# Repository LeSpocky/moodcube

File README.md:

MoodCube
========

What's This?
------------

With mood39 aka Starterkit from [Netz39](http://www.netz39.de/) and the
[infinity mirror cube](http://www.netz39.de/projekte/infinitiy-mirror-cube/) 
from Frank in mind I designed a mood lamp with five RGB LEDs, three
potentiometers and an ATtiny 24/44 controller.

Circuits
--------

Eagle files for both types of PCB are included. One is the base with the
microcontroller and the potentiometers. VCC is intended to be 5V,
however in the first prototype there's no voltage control circuit on
this pcb, so you have to connect a stabilized power supply.

The other one is a PCB for the LED. Current is hold constant by a simple
constant current circuit per color channel. The connection is simply one
cable per channel plus VCC and GND. uC I/O ports are directly connected
to the color lines.

Housing
-------

The housing in the prototype was 6mm plexiglass milled on a CNC machine.
Holding it together was forgotten in design, but the OpenSCAD files are
added here anyway. Simply glueing them is one solution. You could also
make a base plate or anything else.

LED-PCB Mount
-------------

For the prototype I used a frame construction printed with a 3D printer
and lots of hot melt glue. However this was far from optimal and should
not repeated! Please think up a better solution and let me know!

Part List
---------
/tbd/

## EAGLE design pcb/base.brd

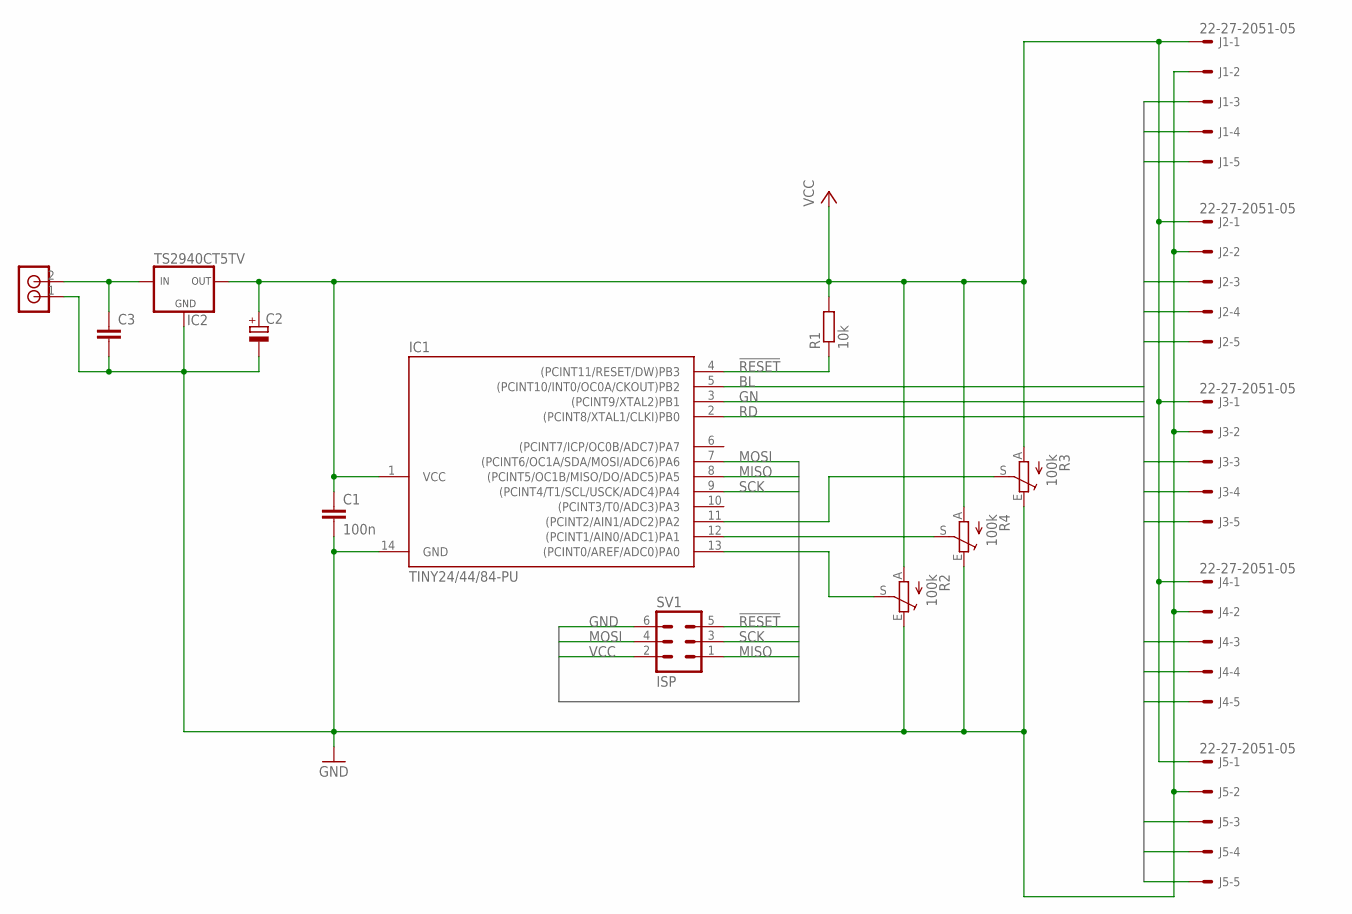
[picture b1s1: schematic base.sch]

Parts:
C1: 100n; C0805
C2: CPOL-EUE2.5-7; E2,5-7
C3: C-EU025-025X050; C025-025X050
IC1: TINY24/44/84-PU; DIL14
IC2: TS2940CT5TV; TO220V
J1, J2, J3, J4, J5: 22-27-2051-05; 6410-05
R1: 10k; R0805
R2, R3, R4: 100k; CIP20C-6MM
SV1: ISP; ML6
U$9: RIACON_101_2

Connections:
!RESET: IC1.4 ((PCINT11/RESET/DW)PB3), R1.1, SV1.5
BL: IC1.5 ((PCINT10/INT0/OC0A/CKOUT)PB2), J1.5, J2.5, J3.5, J4.5, J5.5
GN: IC1.3 ((PCINT9/XTAL2)PB1), J1.4, J2.4, J3.4, J4.4, J5.4
GND: C1.2, C2.-, C3.2, IC1.14 (GND), IC2.2 (GND), J1.2, J2.2, J3.2, J4.2, J5.2, R2.E, R3.E, R4.E, SV1.6, U$9.1
MISO: IC1.8 ((PCINT5/OC1B/MISO/DO/ADC5)PA5), SV1.1
MOSI: IC1.7 ((PCINT6/OC1A/SDA/MOSI/ADC6)PA6), SV1.4
unnamed: IC1.13 ((PCINT0/AREF/ADC0)PA0), R2.S
unnamed: IC1.12 ((PCINT1/AIN0/ADC1)PA1), R4.S
unnamed: IC1.11 ((PCINT2/AIN1/ADC2)PA2), R3.S
unnamed: C3.1, IC2.1 (IN), U$9.2
RD: IC1.2 ((PCINT8/XTAL1/CLKI)PB0), J1.3, J2.3, J3.3, J4.3, J5.3
SCK: IC1.9 ((PCINT4/T1/SCL/USCK/ADC4)PA4), SV1.3
VCC: C1.1, C2.+, IC1.1 (VCC), IC2.3 (OUT), J1.1, J2.1, J3.1, J4.1, J5.1, R1.2, R2.A, R3.A, R4.A, SV1.2

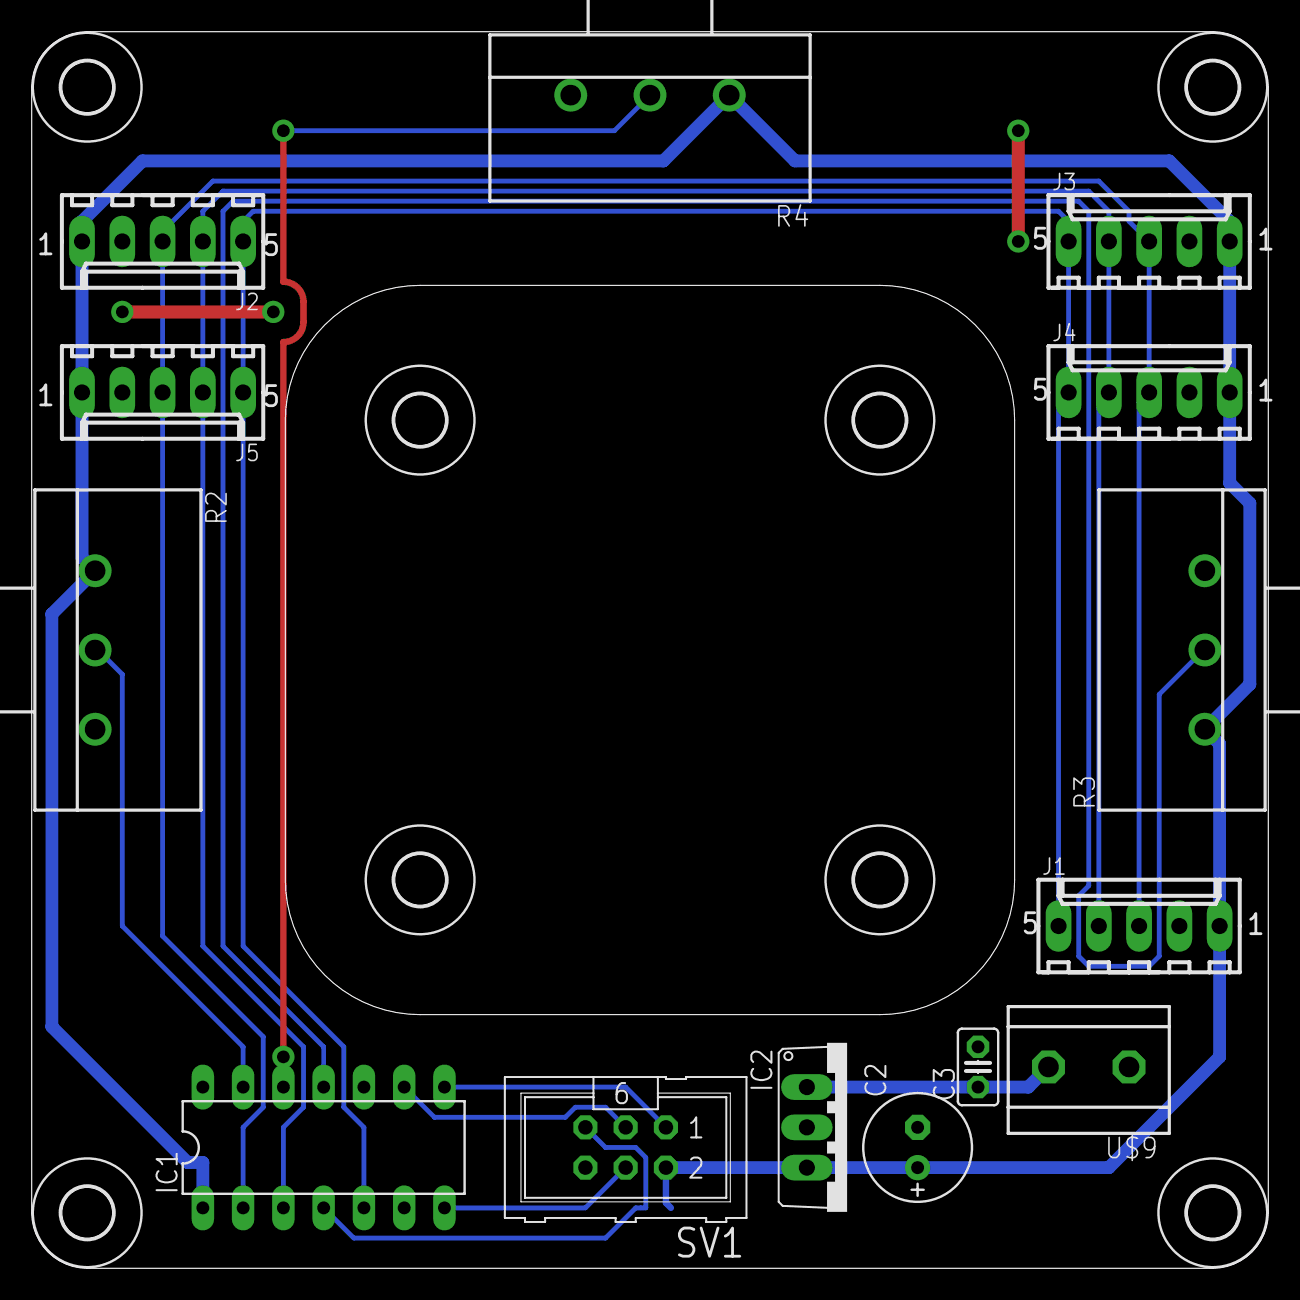
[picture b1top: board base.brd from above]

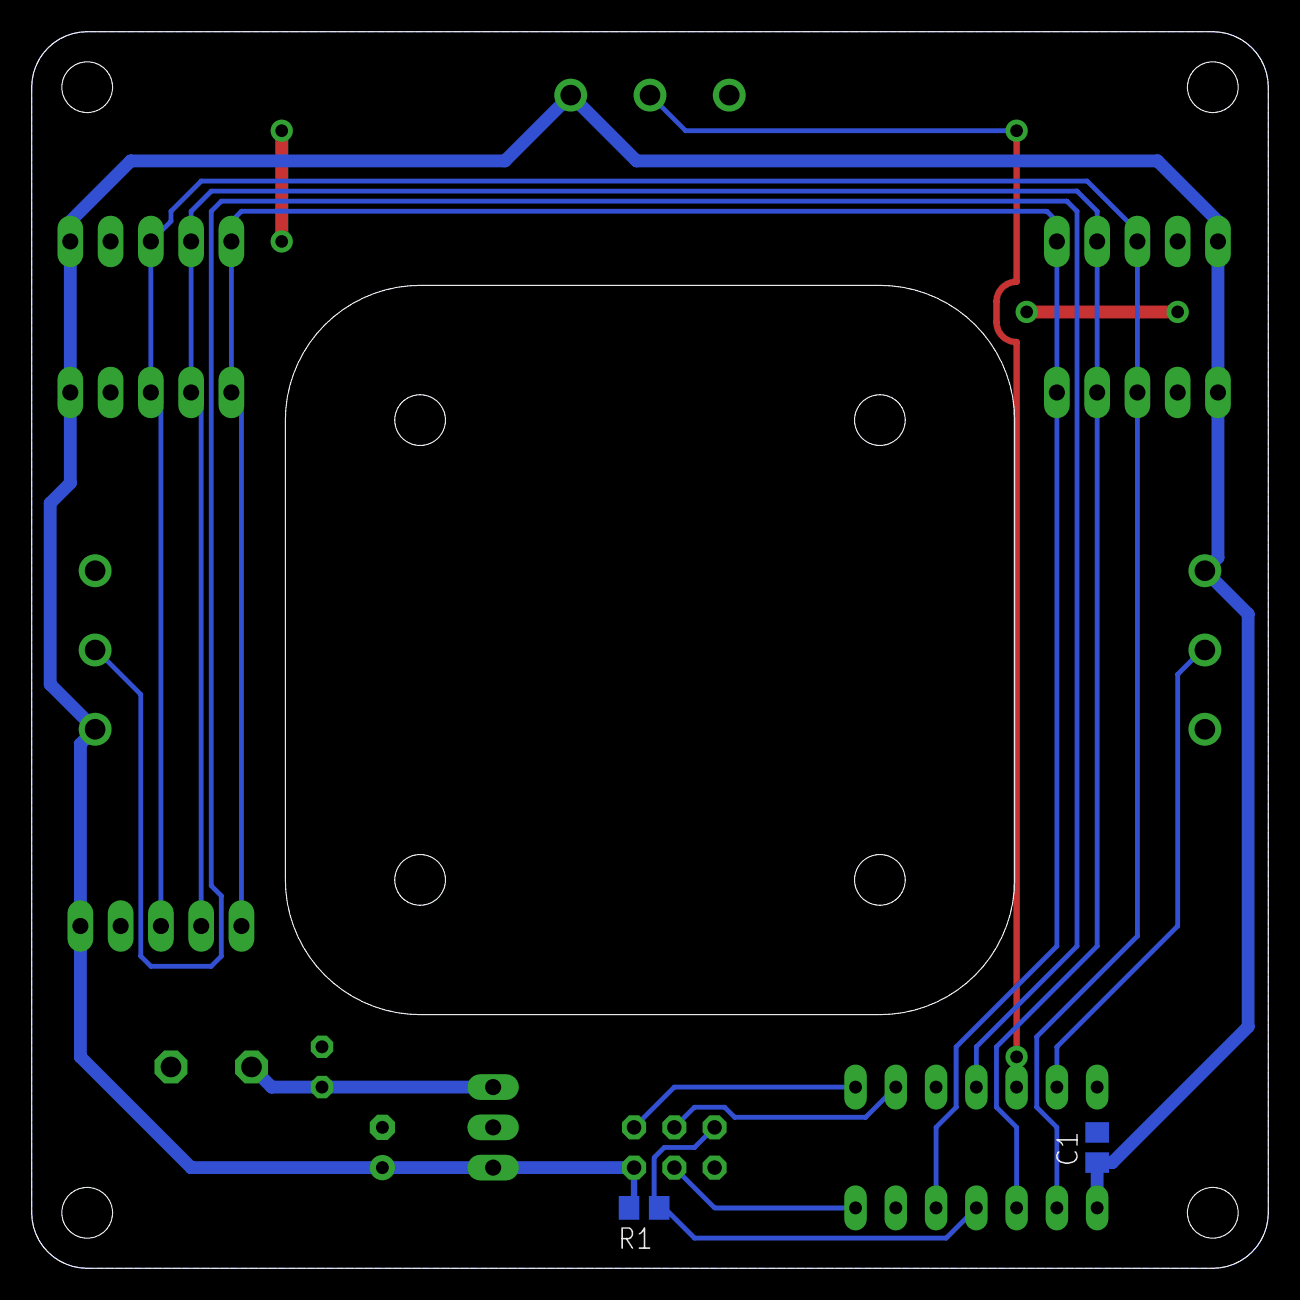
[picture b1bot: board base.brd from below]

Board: 2 copper layers, 78.0 x 78.0 mm, 24 parts (2 on the bottom side), 13 nets.

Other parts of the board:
U$1, U$2, U$3, U$4, U$5, U$6, U$7, U$8: 3,2

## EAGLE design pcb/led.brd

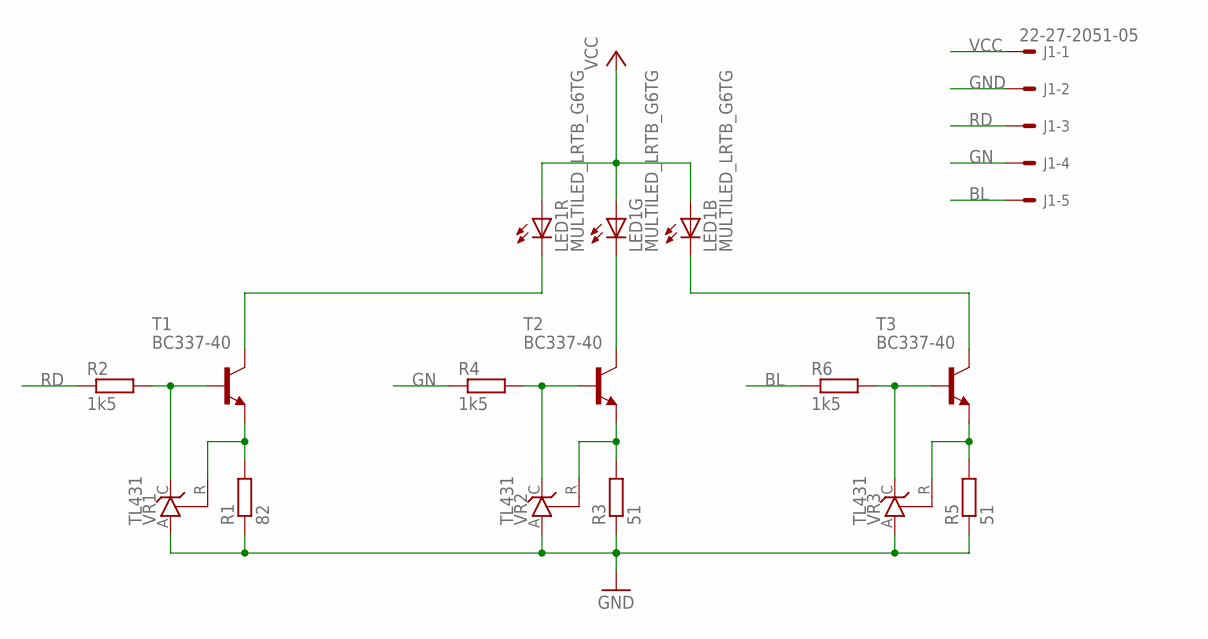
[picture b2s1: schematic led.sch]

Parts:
J1: 22-27-2051-05; 6410-05
LED1: MULTILED_LRTB_G6TG; P-LCC-6_TOPLED
R1: 82; 0207/7
R2, R6: 1k5; R0805
R3, R5: 51; 0207/7
R4: 1k5; 0207/10
T1, T2, T3: BC337-40; TO92-CBE
VR1, VR2, VR3: TL431; TO92-CLP

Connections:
BL: J1.5, R6.1
GN: J1.4, R4.1
GND: J1.2, R1.1, R3.1, R5.1, VR1.A, VR2.A, VR3.A
unnamed: R1.2, T1.E, VR1.R
unnamed: R3.2, T2.E, VR2.R
unnamed: R2.2, T1.B, VR1.C
unnamed: R4.2, T2.B, VR2.C
unnamed: LED1.C1 (C), T1.C
unnamed: LED1.C2 (C), T2.C
RD: J1.3, R2.1
T3_B-C: R6.2, T3.B, VR3.C
T3_C: LED1.C3 (C), T3.C
T3_E-R: R5.2, T3.E, VR3.R
VCC: J1.1, LED1.A1 (A), LED1.A2 (A), LED1.A3 (A)

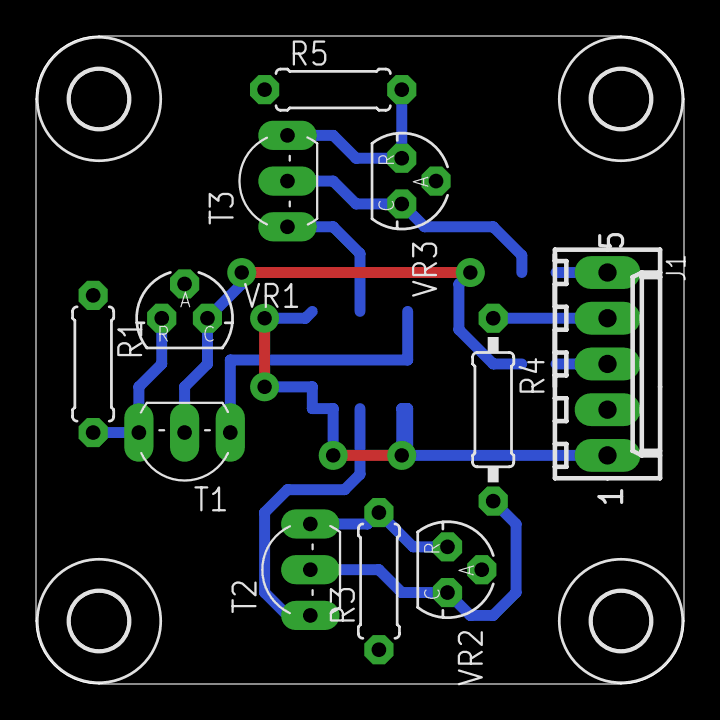
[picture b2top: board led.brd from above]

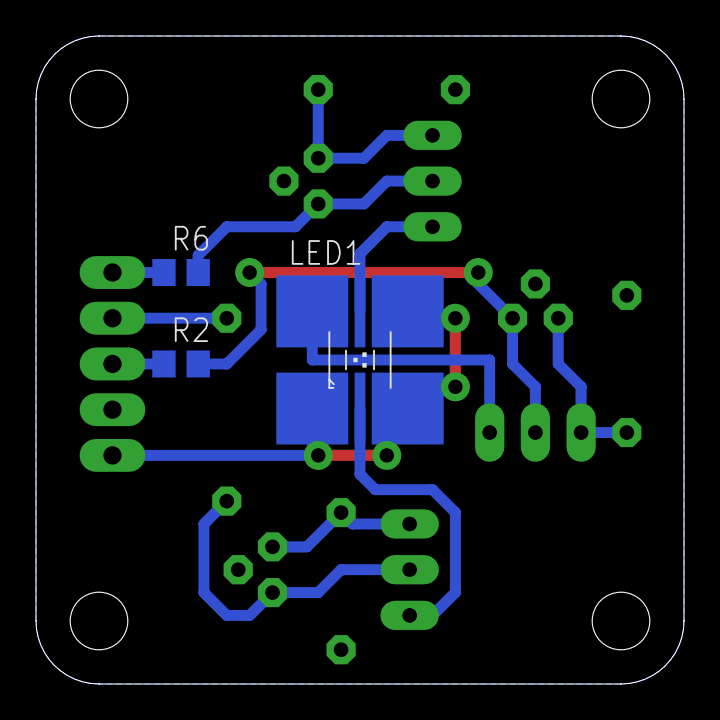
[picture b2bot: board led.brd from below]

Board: 2 copper layers, 36.0 x 36.0 mm, 18 parts (3 on the bottom side), 14 nets.

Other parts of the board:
U$1, U$2, U$3, U$4: 3,2

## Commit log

2013-12-22 initial
2013-12-22 import hsv2rgb
2013-12-23 add bsize init and add hsv2rgb to Makefile dependencies
2013-12-23 copied timer and pwm stuff from avr101
2013-12-23 add ADC stuff and adapt to attiny24 and 3 channels
2013-12-23 use hsv2rgb instead of rgb
2013-12-29 fix color
2013-12-29 added pcb files, one cad file, and added some stuff to readme
2014-01-05 use a 9 bit PWM and a 256 step lookup table
2014-01-06 add voltage regulator and other clamp
2014-01-07 route voltage regulator
2014-01-07 add git ignore list
